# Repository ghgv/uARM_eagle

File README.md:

# uARM_eagle
This is a PCB and schematic for an Leonardo Microcontroller

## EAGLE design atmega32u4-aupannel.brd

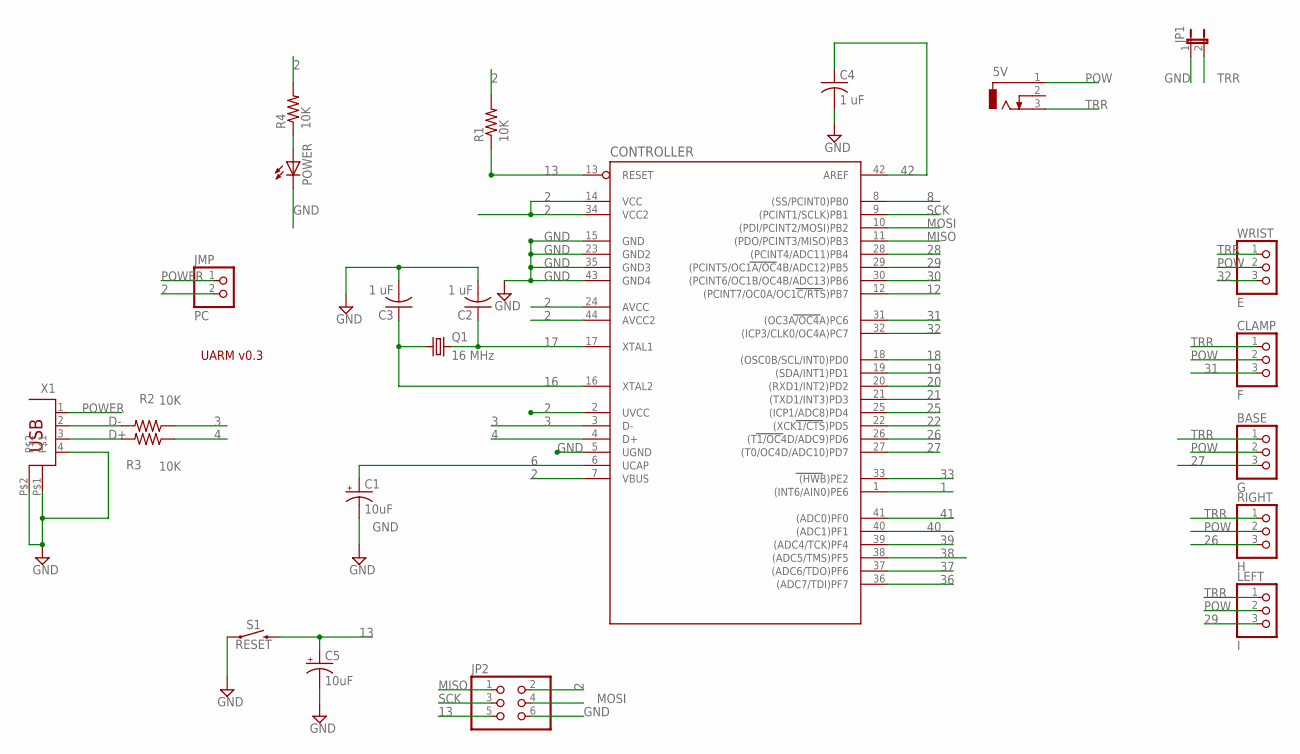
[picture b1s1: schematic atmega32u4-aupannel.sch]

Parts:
5V: DCJ0202
BASE: G; 1X03
C1, C5: 10uF; CPOL-RADIAL-2.5MM-5MM-KIT
C2, C3, C4: 1 uF; C025-024X044
CLAMP: F; 1X03
CONTROLLER: ATMEGA32U4-AU; TQFP44
JMP: PC; 1X02
JP1: JP1E; JP1
JP2: PINHD-2X3; 2X03
LEFT: I; 1X03
POWER: LEDCHIPLED_0805; CHIPLED_0805
Q1: 16 MHz; HC18U-V
R1, R2, R3, R4: 10K; M0805
RIGHT: H; 1X03
S1: RESET; TACTILE_SWITCH_PTH_6.0MM
WRIST: E; 1X03
X1: PN61729

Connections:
1: CONTROLLER.1 ((INT6/AIN0)PE6)
2: CONTROLLER.2 (UVCC), CONTROLLER.7 (VBUS), CONTROLLER.14 (VCC), CONTROLLER.24 (AVCC), CONTROLLER.34 (VCC2), CONTROLLER.44 (AVCC2), JMP.2, JP2.2, R1.2, R4.2
3: CONTROLLER.3 (D-), R2.1
4: CONTROLLER.4 (D+), R3.1
6: C1.1 (+), CONTROLLER.6 (UCAP)
8: CONTROLLER.8 ((SS/PCINT0)PB0)
12: CONTROLLER.12 ((PCINT7/OC0A/OC1C/RTS)PB7)
13: C5.1 (+), CONTROLLER.13 (RESET), JP2.5, R1.1, S1.3 (2)
16: C3.1, CONTROLLER.16 (XTAL2), Q1.1
17: C2.1, CONTROLLER.17 (XTAL1), Q1.2
18: CONTROLLER.18 ((OSC0B/SCL/INT0)PD0)
19: CONTROLLER.19 ((SDA/INT1)PD1)
20: CONTROLLER.20 ((RXD1/INT2)PD2)
21: CONTROLLER.21 ((TXD1/INT3)PD3)
22: CONTROLLER.22 ((XCK1/CTS)PD5)
25: CONTROLLER.25 ((ICP1/ADC8)PD4)
26: CONTROLLER.26 ((T1/OC4D/ADC9)PD6), RIGHT.3
27: BASE.3, CONTROLLER.27 ((T0/OC4D/ADC10)PD7)
28: CONTROLLER.28 ((PCINT4/ADC11)PB4)
29: CONTROLLER.29 ((PCINT5/OC1A/OC4B/ADC12)PB5), LEFT.3
30: CONTROLLER.30 ((PCINT6/OC1B/OC4B/ADC13)PB6)
31: CLAMP.3, CONTROLLER.31 ((OC3A/OC4A)PC6)
32: CONTROLLER.32 ((ICP3/CLK0/OC4A)PC7), WRIST.3
33: CONTROLLER.33 ((HWB)PE2)
36: CONTROLLER.36 ((ADC7/TDI)PF7)
37: CONTROLLER.37 ((ADC6/TDO)PF6)
38: CONTROLLER.38 ((ADC5/TMS)PF5)
39: CONTROLLER.39 ((ADC4/TCK)PF4)
40: CONTROLLER.40 ((ADC1)PF1)
41: CONTROLLER.41 ((ADC0)PF0)
42: C4.1, CONTROLLER.42 (AREF)
D+: R3.2, X1.3
D-: R2.2, X1.2
GND: C1.2 (-), C2.2, C3.2, C4.2, C5.2 (-), CONTROLLER.5 (UGND), CONTROLLER.15 (GND), CONTROLLER.23 (GND2), CONTROLLER.35 (GND3), CONTROLLER.43 (GND4), JP1.1, JP2.6, POWER.C, S1.1, X1.4, X1.P$1, X1.P$2
MISO: CONTROLLER.11 ((PDO/PCINT3/MISO)PB3), JP2.1
MOSI: CONTROLLER.10 ((PDI/PCINT2/MOSI)PB2), JP2.4
unnamed: POWER.A, R4.1
POW: 5V.1, BASE.2, CLAMP.2, LEFT.2, RIGHT.2, WRIST.2
POWER: JMP.1, X1.1
SCK: CONTROLLER.9 ((PCINT1/SCLK)PB1), JP2.3
TRR: 5V.3, BASE.1, CLAMP.1, JP1.2, LEFT.1, RIGHT.1, WRIST.1

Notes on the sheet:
UARM v0.3

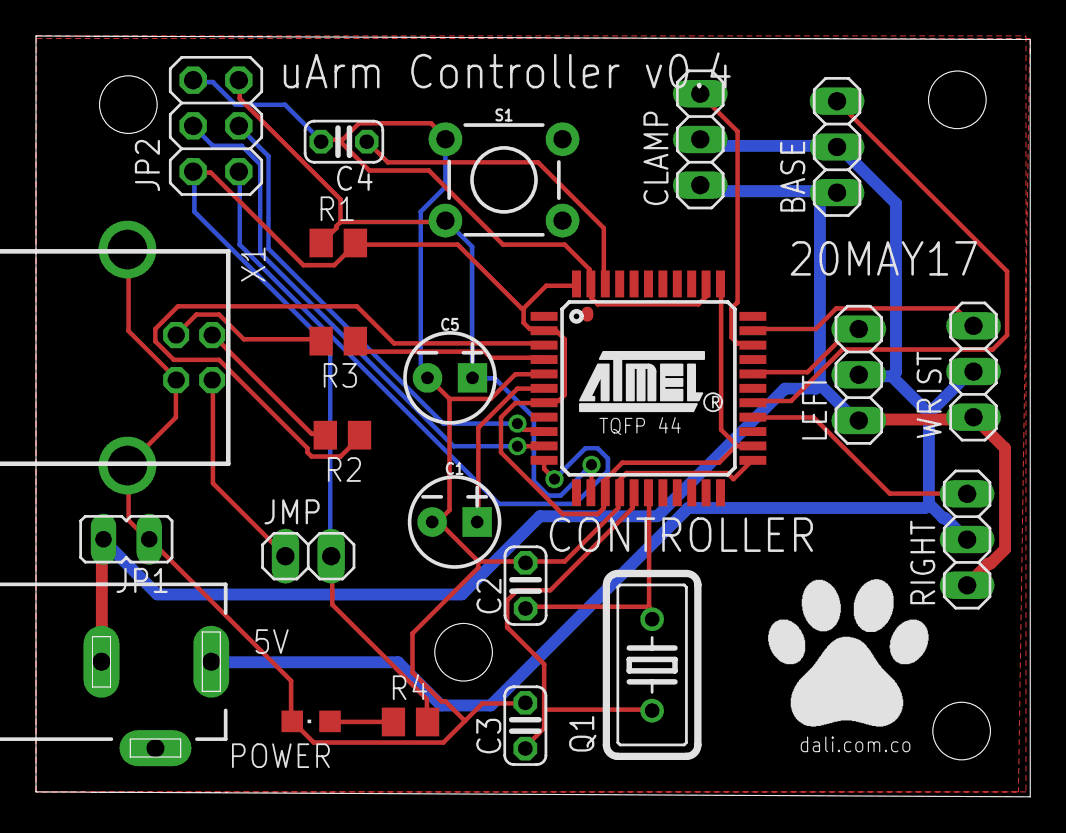
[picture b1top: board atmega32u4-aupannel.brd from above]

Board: 2 copper layers, 55.2 x 42.3 mm, 24 parts (0 on the bottom side), 23 nets.

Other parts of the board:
U$1: DALI

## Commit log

2019-11-14 Version of the 20th of May 2017

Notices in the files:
parts and their libraries:
SparkFun-Capacitors: Licensing: Creative Commons ShareAlike 4.0 International - https://creativecommons.org/licenses/by-sa/4.0
